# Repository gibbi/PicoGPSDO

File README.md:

# picoExtRef — GPS-disciplined OCXO reference (Pico)

RP2040 firmware that steers an OCXO via PWM (“DAC”), reads u-blox GNSS time over UART (UBX), and closes a two-stage servo: coarse steering from NAV-CLOCK and fine steering from TIM-TP `qErr`. A small Flask dashboard on the host tails USB CDC for live plots and tuning.

**Hardware upstream:** this tree is based on [gibbi/PicoGPSDO](https://github.com/gibbi/PicoGPSDO) (schematics, KiCad, and notes under `hardware/`). Presentation context: European GNU Radio Days 2024 — [talk on YouTube](https://www.youtube.com/watch?v=h3X4QuF_BUM).

---

## Web UI screenshot

## Repository layout and components

| Area | Role |
|------|------|
| **`src/main.c`** | Boot, PWM DAC / 26 MHz ref clock, main loop, JSON telemetry, USB CLI polling, fine-mode edge tracker integration, fractional DAC accumulation. |
| **`src/ubx.c`**, **`src/ubx_rx.c`** | UART RX (frame assembly + checksum), UBX decode, fills `current_gps_data` (NAV-CLOCK, TIM-TP, PVT, etc.). |
| **`include/ubx_clean.h`** | Shared GPS/UBX structs and packet layout used by the parser. |
| **`src/gpsdo_control.c`**, **`include/gpsdo_control.h`** | Finelock hysteresis, coarse/fine control outputs (`u_ns`), NAV-CLOCK bias handling, telemetry `tr` flags. |
| **`src/gpsdo_tune.c`**, **`include/gpsdo_tune.h`** | Runtime tunables and USB one-line CLI (`kp`, `fine_mode`, gates, etc.). |
| **`include/display.h`** | SSD1306 OLED over I2C (optional); live status text on the module. |
| **`pico_gpsdo_web.py`** | Flask host app: reads Pico USB serial, parses `{…}` telemetry, serves charts, tune forms, log tail, optional series clear. |
| **`pico.py`** | Developer entrypoint: `clean` / `build` / `flash` / `webserver` / `lint` (see script header for caveats on `build/` paths). |
| **`CMakeLists.txt`**, **`boards/`** | Pico SDK project, board hooks. |
| **`hardware/`** | From [PicoGPSDO](https://github.com/gibbi/PicoGPSDO): PCB and hardware documentation (see `hardware/Readme.md`). |
| **`tests/`** | Small host-side tests (e.g. UBX RX framing). |

---

## Data flow (short)

1. **u-blox** → UART0 → UBX frames → `current_gps_data` (`clkB`, `qErr`, `dac`, fix, etc.).
2. **Servo** (when `mode servo`): coarse on `clkD_bias` when bias steps; fine on `qErr` (P-only or edge mode) in finelock.
3. **USB CDC** → compact JSON lines for the host **web UI** and `printf` debugging.

---

## Quick start

```bash
# Firmware (needs Pico SDK in environment per Pico docs)
./pico.py build
./pico.py flash          # optional: ./pico.py flash --webserver

# Web dashboard only (USB serial to the Pico)
pip install -r requirements.txt
./pico.py webserver      # or: python3 pico_gpsdo_web.py … per pico.py usage
```

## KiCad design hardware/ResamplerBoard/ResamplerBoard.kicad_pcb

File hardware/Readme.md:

# Hardware Description

This folder holds the hardware documentation for the 26MHz testbed. 

## Todo:

- [x] push kicad projects
- [ ] document antennuator values
- [ ] document ublox modification
- [ ] document oscillator swap

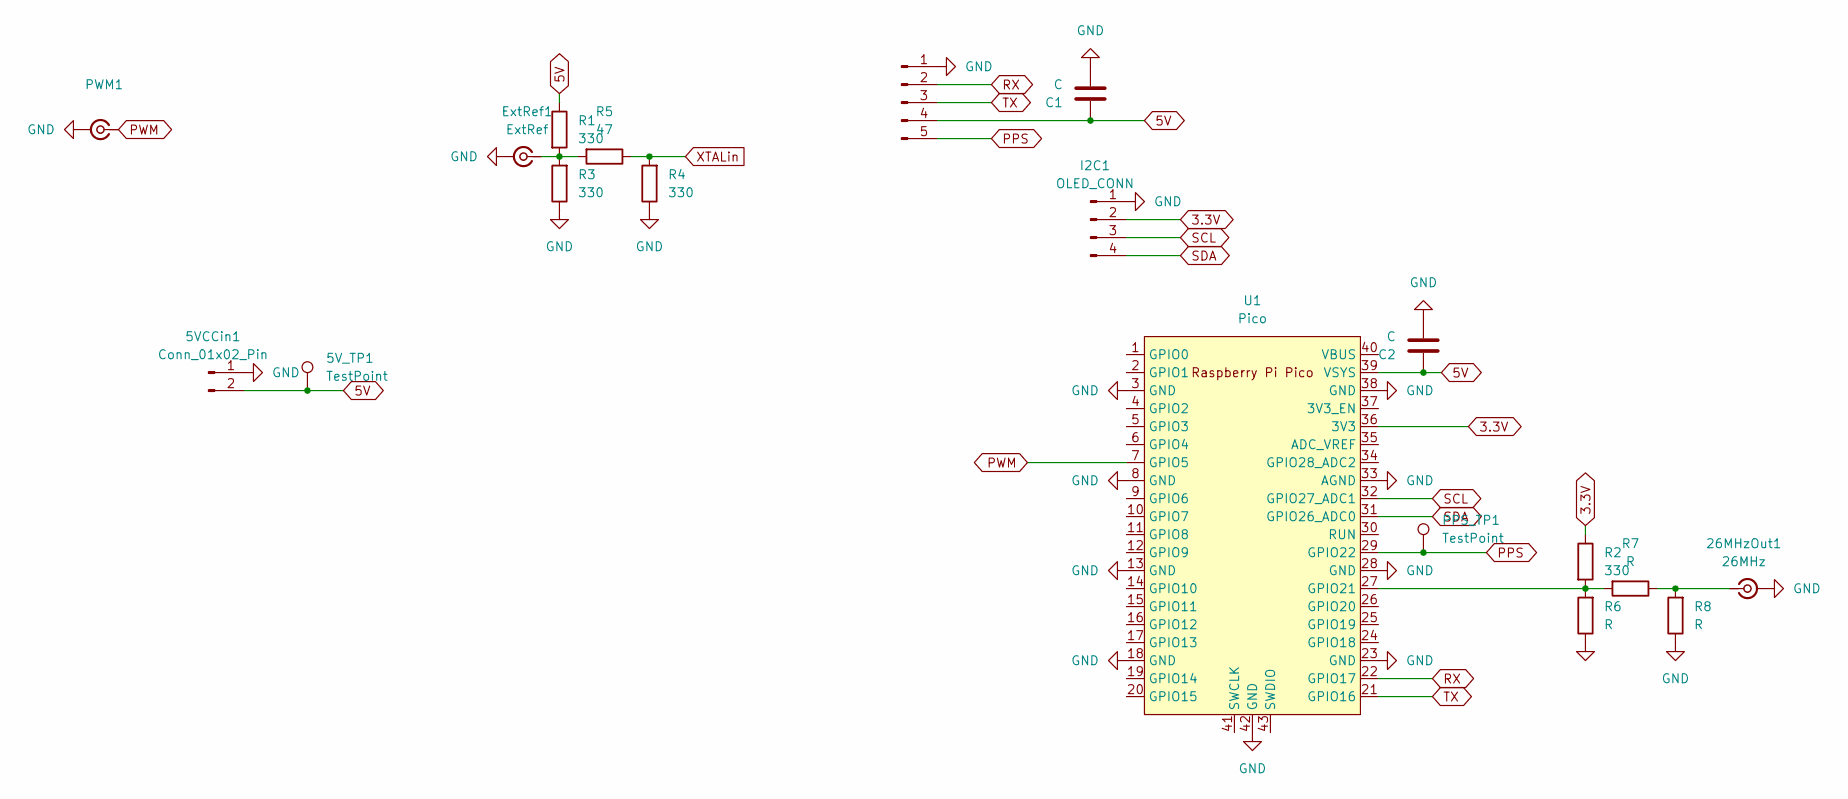
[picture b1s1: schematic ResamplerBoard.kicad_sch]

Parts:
5VCCin1: Conn_01x02_Pin; PinHeader_1x02_5VIN
5V_TP1: TestPoint; TestPoint_Pad_D2.0mm
26MHzOut1: 26MHz; SMA_EDGE_GIBBI
C1, C2: C; C_1210_3225Metric_Pad1.33x2.70mm_HandSolder
ExtRef1: ExtRef; SMA_EDGE_GIBBI
GPS_UART1: 9600; GPS_HEADER
I2C1: OLED_CONN; 128x64OLED
PPS_TP1: TestPoint; TestPoint_Pad_D2.0mm
PWM1: PWM; SMA_EDGE_GIBBI
R1, R2, R3, R4: 330; R_1210_3225Metric_Pad1.30x2.65mm_HandSolder
R5: 47; R_1210_3225Metric_Pad1.30x2.65mm_HandSolder
R6, R7, R8: R; R_1210_3225Metric_Pad1.30x2.65mm_HandSolder
U1: Pico; RPi_Pico_SMD_TH_NO_SILK_NO_HOLE

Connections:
3.3V: I2C1.2, R2.1, U1.36 (3V3)
5V: 5VCCin1.2, 5V_TP1.1, C1.1, C2.1, GPS_UART1.4, R1.1, U1.39 (VSYS)
GND: 5VCCin1.1, 26MHzOut1.2 (Ext), C1.2, C2.2, ExtRef1.2 (Ext), GPS_UART1.1, I2C1.1, PWM1.2 (Ext), R3.1, R4.1, R6.1, R8.1, U1.3 (GND), U1.8 (GND), U1.13 (GND), U1.18 (GND), U1.23 (GND), U1.28 (GND), U1.33 (AGND), U1.38 (GND), U1.42 (GND)
unnamed: 26MHzOut1.1 (In), R7.1, R8.2
unnamed: ExtRef1.1 (In), R1.2, R3.2, R5.2
unnamed: R2.2, R6.2, R7.2, U1.27 (GPIO21)
PPS: GPS_UART1.5, PPS_TP1.1, U1.29 (GPIO22)
PWM: PWM1.1 (In), U1.7 (GPIO5)
RX: GPS_UART1.2, U1.22 (GPIO17)
SCL: I2C1.3, U1.32 (GPIO27_ADC1)
SDA: I2C1.4, U1.31 (GPIO26_ADC0)
TX: GPS_UART1.3, U1.21 (GPIO16)
XTALin: R4.2, R5.1

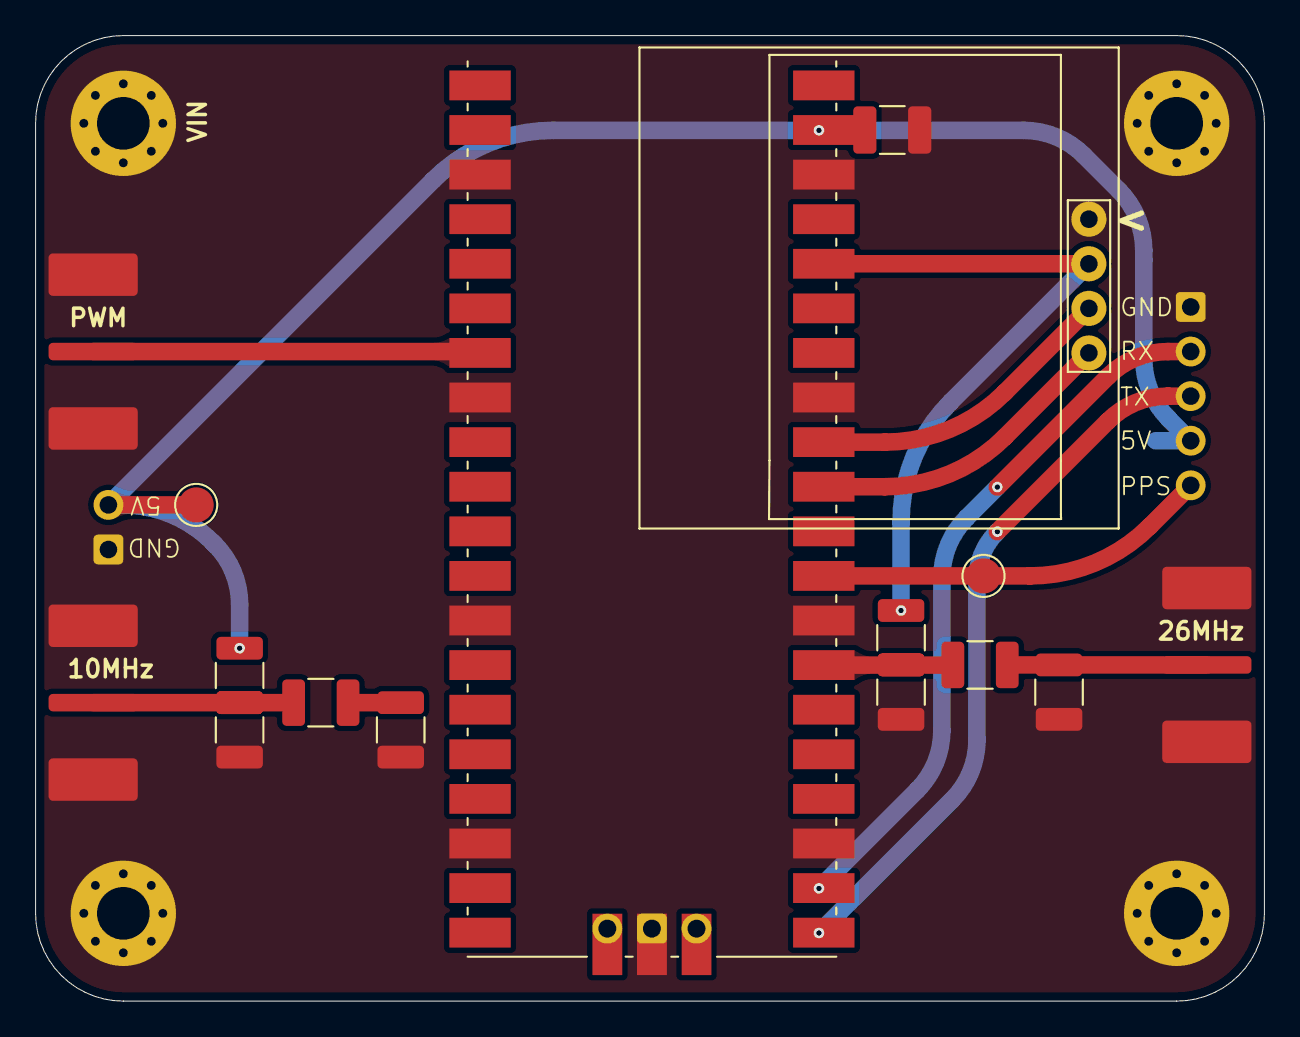
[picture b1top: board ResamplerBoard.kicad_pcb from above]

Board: 2 copper layers, 70.0 x 55.0 mm, 19 parts (1 on the bottom side), 13 nets.

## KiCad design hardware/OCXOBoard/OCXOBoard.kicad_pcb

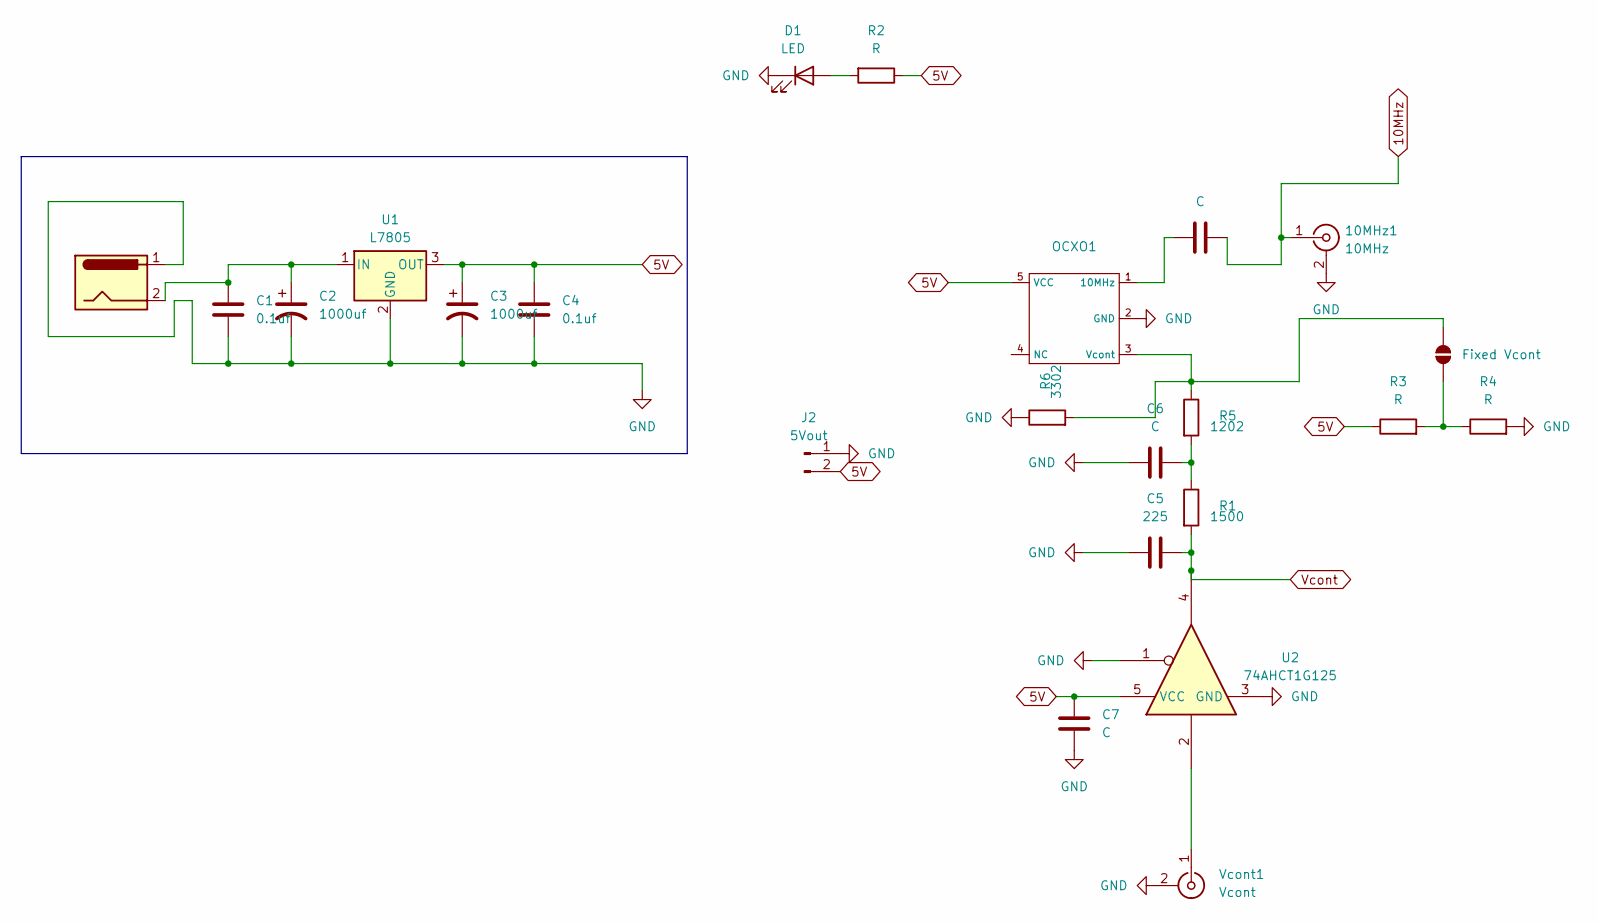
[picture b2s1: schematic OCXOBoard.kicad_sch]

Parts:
10MHz1: 10MHz; SMA_EDGE_GIBBI
C1, C4: 0.1uf; C_1210_3225Metric_Pad1.33x2.70mm_HandSolder
C2, C3: 1000uf; CP_EIA-7343-43_Kemet-X_Pad2.25x2.55mm_HandSolder
C5: 225; C_1210_3225Metric_Pad1.33x2.70mm_HandSolder
C6, C7: C; C_1210_3225Metric_Pad1.33x2.70mm_HandSolder
C8: C; C_0805_2012Metric_Pad1.18x1.45mm_HandSolder
D1: LED; D_1210_3225Metric_Pad1.42x2.65mm_HandSolder
FixedVcont1: Fixed Vcont; SolderJumper-2_P1.3mm_Open_RoundedPad1.0x1.5mm
J1: DC Connector; AMASS_XT30PW-M_1x02_P2.50mm_Horizontal
J2: 5Vout; Simple5V
OCXO1: MULTI_XO
R1: 1500; R_1210_3225Metric_Pad1.30x2.65mm_HandSolder
R2, R3, R4: R; R_1210_3225Metric_Pad1.30x2.65mm_HandSolder
R5: 1202; R_1210_3225Metric_Pad1.30x2.65mm_HandSolder
R6: 3302; R_1210_3225Metric_Pad1.30x2.65mm_HandSolder
U1: L7805; TO-7805
U2: 74AHCT1G125; SOT-23-5_HandSoldering
Vcont1: Vcont; SMA_EDGE_GIBBI

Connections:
5V: C3.1, C4.1, C7.2, J2.2, OCXO1.5 (VCC), R2.1, R3.1, U1.3 (OUT), U2.5 (VCC)
10MHz: 10MHz1.1 (In), C8.2
GND: 10MHz1.2 (Ext), C1.2, C2.2, C3.2, C4.2, C5.1, C6.1, C7.1, D1.1 (K), J1.1, J2.1, OCXO1.2 (GND), R4.2, R6.1, U1.2 (GND), U2.1, U2.3 (GND), Vcont1.2 (Ext)
unnamed: C6.2, R1.1, R5.2
unnamed: D1.2 (A), R2.2
unnamed 5: FixedVcont1.1 (A), R3.2, R4.1; also elsewhere on the board
unnamed 6: FixedVcont1.2 (B), OCXO1.3 (Vcont), R5.1, R6.2; also elsewhere on the board
unnamed: C8.1, OCXO1.1 (10MHz)
unnamed: C1.1, C2.1, J1.2, U1.1 (IN)
unnamed: U2.2, Vcont1.1 (In)
Vcont: C5.2, R1.2, U2.4

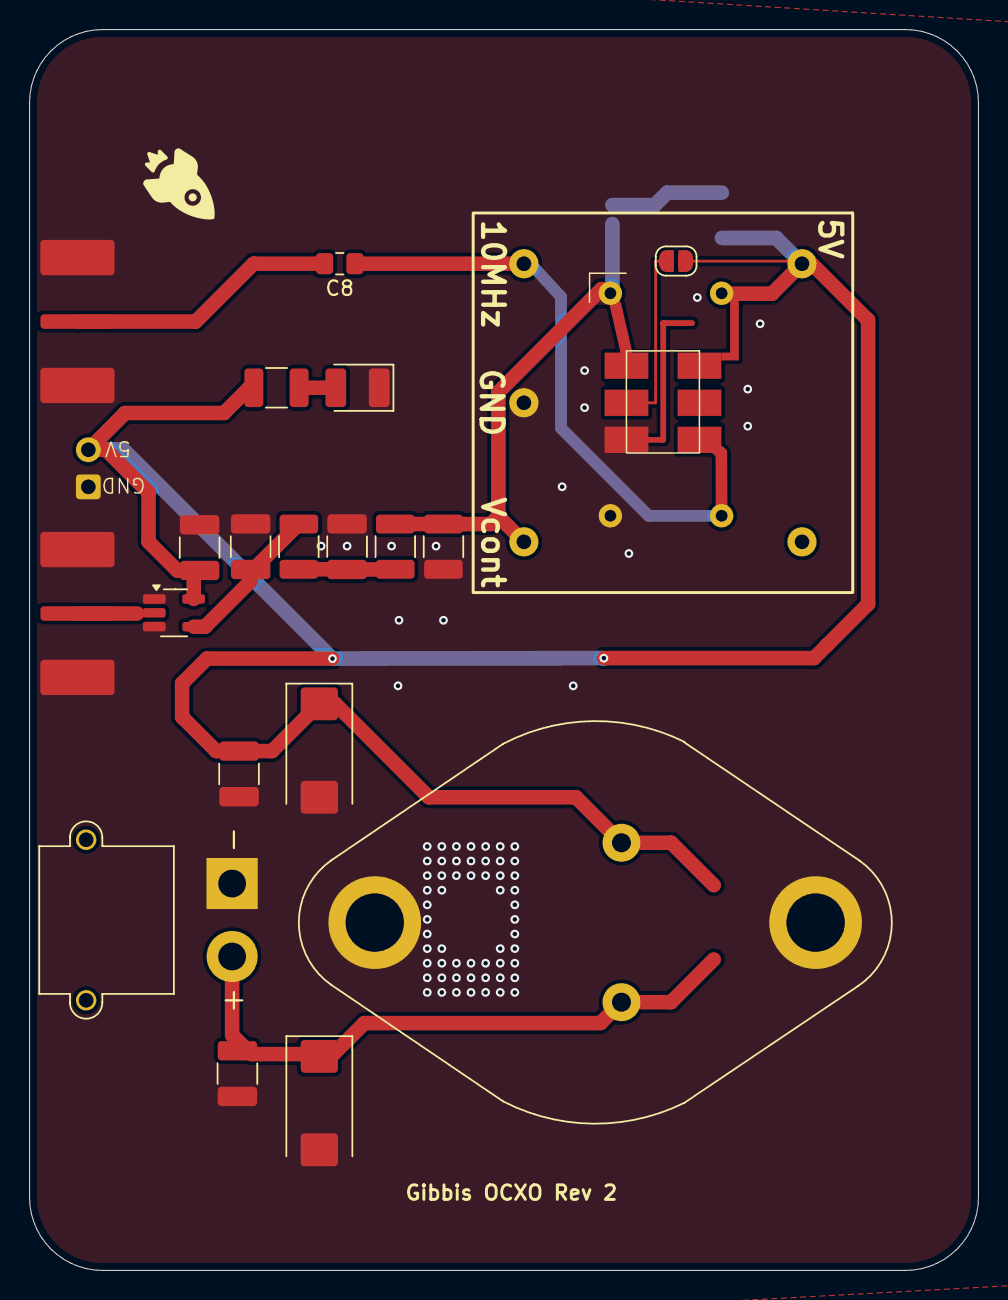
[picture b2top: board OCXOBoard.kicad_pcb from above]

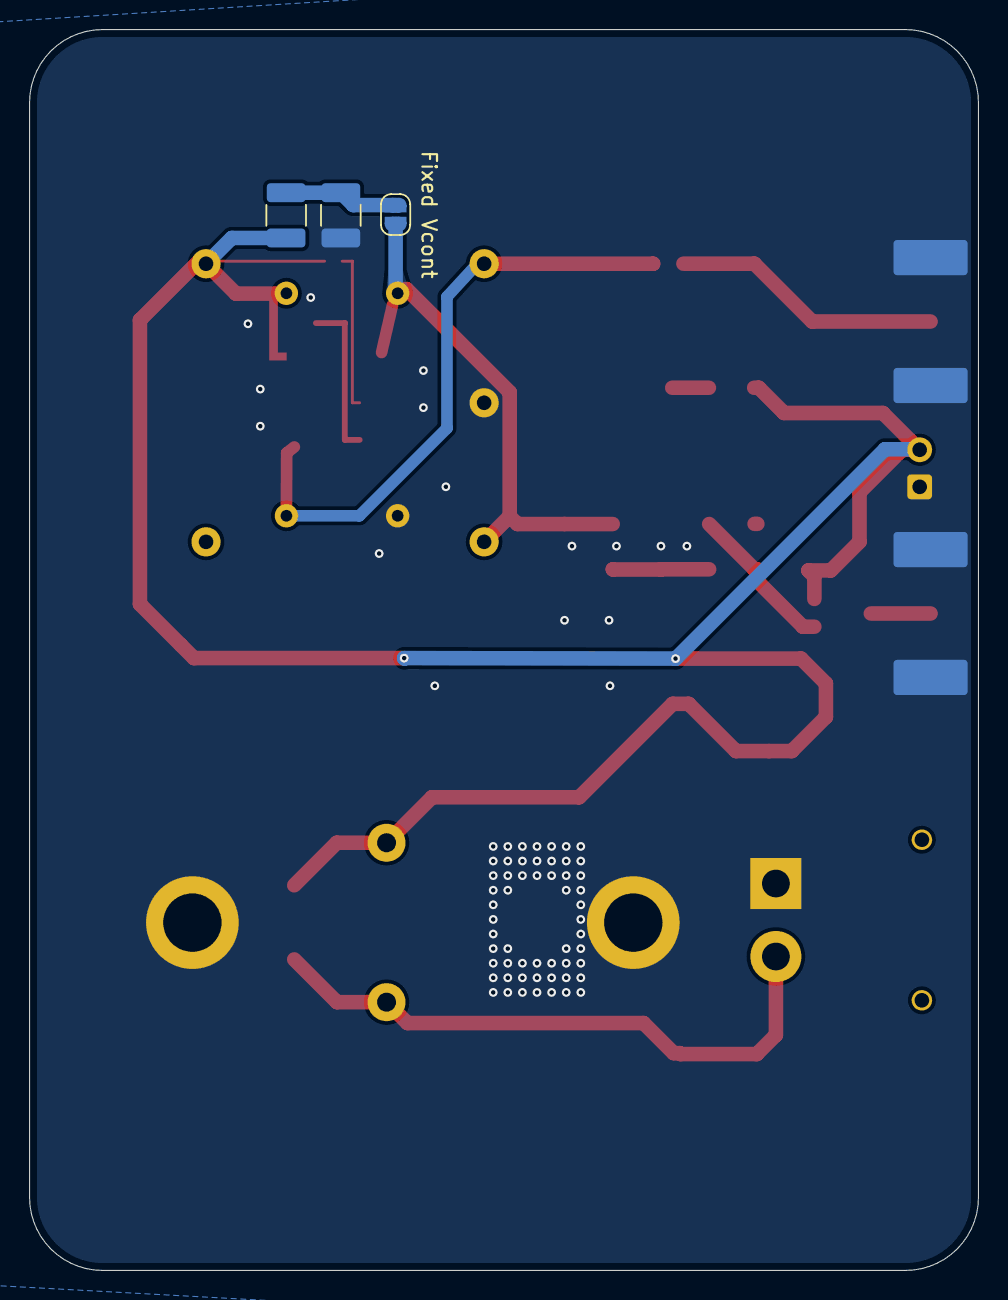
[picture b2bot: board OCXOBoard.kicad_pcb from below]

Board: 2 copper layers, 65.0 x 85.0 mm, 24 parts (3 on the bottom side), 11 nets.

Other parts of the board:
FixedVcont1#2: Fixed Vcont; SolderJumper-2_P1.3mm_Open_RoundedPad1.0x1.5mm

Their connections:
unnamed 5: FixedVcont1#2.1 (A); also elsewhere on the board
unnamed 6: FixedVcont1#2.2 (B); also elsewhere on the board

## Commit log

2024-09-03 add hardware
2026-04-20 init
2026-04-20 documentation
